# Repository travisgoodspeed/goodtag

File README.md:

# GoodTag

Howdy y'all!

For a long while I've been interested in the RF430FRL152H, which is a
passive RFID tag for 13.56 MHz built around an MSP430 microcontroller.
As few open source examples were available, I found myself first
building a development kit

In this repository, and its
[wiki](https://github.com/travisgoodspeed/goodtag/wiki), you will find
examples and documentation for programming this fine chip, as well as
CAD for hardware boards that use the chip.  This should help you build
your own NFC Type V (ISO 15693) sensor tags, or to emulate existing ones.

This project cannot implement ISO 7816 or ISO 14443 interfaces of
older NFC tags.  For that, you probably need a board designed around
the LPC8N04 or some other microcontroller.

It has partial support for the RF430TAL152H chip found in some medical
devices, written as part of a research project with Axelle Apvrille,
which we presented as [The Inner Guts of a Connected Glucose Sensor
for
Diabetes](https://github.com/cryptax/talks/blob/master/BlackAlps-2019/glucose-blackalps2019.pdf)
at BlackAlps 2019.

73 from Yverdon les Bains,

--Travis Goodspeed

## Getting Started

See the
[GettingStarted](https://github.com/travisgoodspeed/goodtag/wiki/GettingStarted)
page of the wiki for details on how to begin.  You will need an
assembled board, a Linux shell account, and a recent Android phone,
such as the Pixel 3.

## Toolchain

The C examples in this project *must* be compiled with TI's branch of
[GCC for
MSP430](http://software-dl.ti.com/msp430/msp430_public_sw/mcu/msp430/MSPGCC/latest/index_FDS.html).
We sadly cannot be compatible with the GCC4 branch shipped with Debian
because the function calling conventions are incompatible with the
mask ROM.  You will need both the toolchain and its support files.

See my [GoodV](https://github.com/travisgoodspeed/GoodV) project for
an example Android app that communicates with the chip over NfcV.  It
can write firmware to the tags in the TI-TXT format, as well as dump
their existing contents.

For convenient programming from Linux, the [GreatFET
Hydrangea](https://github.com/travisgoodspeed/hydrangea/) board ought
to be handy.  We'll tie it into the `Makefile` once that project is
functional.

## Documentation

An extensive [goodtag
wiki](https://github.com/travisgoodspeed/goodtag/wiki) covers such
nifty topics as the
[RF430FRL152H](https://github.com/travisgoodspeed/goodtag/wiki/RF430FRL152H)
chip, the contents of [its
ROM](https://github.com/travisgoodspeed/goodtag/wiki/ROM), and the use
of its brother, the otherwise undocumented
[RF430TAL152H](https://github.com/travisgoodspeed/goodtag/wiki/RF430TAL152H).

Axelle Apvrille and Travis Goodspeed presented [The Inner Guts of a
Connected Glucose
Sensor](https://github.com/cryptax/talks/blob/master/BlackAlps-2019/glucose-blackalps2019.pdf)
at BlackAlps 2019, describing a medical sensor that uses the
[RF430TAL152H](https://github.com/travisgoodspeed/goodtag/wiki/RF430TAL152H).

## Firmware

In the `firmware/` directory, you will be find a few example projects.
Most of them are designed to compile as patches to the ROM, hooking
NFC commands rather than being called through the `RESET` vector, so
it's important to remember that global and static variables will *not*
be initialized.

You will probably want to start with `hello.c` and then add your own
vendor extension commands.  `gcmemu.c` is an unfinished emulator for
a commercial glucose sensor tag, and `ndef.c` is an NFC business card
in the NDEF format, which can be read by the
[Decode](https://apps.apple.com/us/app/decode-nfc-scanner/id964303354)
app on an iPhone.

Unlike large applications in which multiple modules are linked
together, this project is organized as individually executable modules
that share no code with one another.  This is considered necessary,
given the pitiful amounts of FRAM code memory.

## Shellcode

In the `shellcode/` directory, you will find short examples of code
that can be run ephemerally from SRAM, without permanent changes to
the target.  See the [Shellcode
page](https://github.com/travisgoodspeed/goodtag/wiki/Shellcode) of
the wiki for a more detailed explanation.

## Hardware Designs

For development, I began by using the
[RF430FRL152HEVM](http://www.ti.com/tool/RF430FRL152HEVM) and
[RF430-TMPSNS-EVM](http://www.ti.com/tool/RF430-TMPSNS-EVM) kits from
Texas Instruments.

As these are now in short supply, I've designed the
[GoodTag11](https://github.com/travisgoodspeed/goodtag/wiki/GoodTag11)
in Kicad as my own development kit.  Expect future designs in this
series.

## Related Projects

[GoodV](https://github.com/travisgoodspeed/GoodV) is an Android app
for interacting with RF430FRL152H devices.  You will probably develop
first with JTAG and then use this to flash your code from a handy
phone.

[The GoodTag Wiki](https://github.com/travisgoodspeed/goodtag/wiki)
contains plenty of documentation about the RF430FRL152H and related
chips.

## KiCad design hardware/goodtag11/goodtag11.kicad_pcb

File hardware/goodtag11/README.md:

Howdy y'all,

The GoodTag11 is my attempt at an NFC tag emulator, based around the
RF430FRL152H chip.

The passive values roughly come from the Texas Instruments reference
design in SLOA247C.  I've brought a few pins out unnecessarily, in
case bodge wires are needed, but they will be more firmly grounded in
future designs.

Manufacture in 2layers, 0.024" thickness, FR4-TG130, 1oz, Immersion
Silver, BLACK SOLDER MASK, TWO SIDE MASK, WHITE SILK SCREEN, TOP SILK,
Complex Shape, 8.560cm x 5.398cm.

--Travis

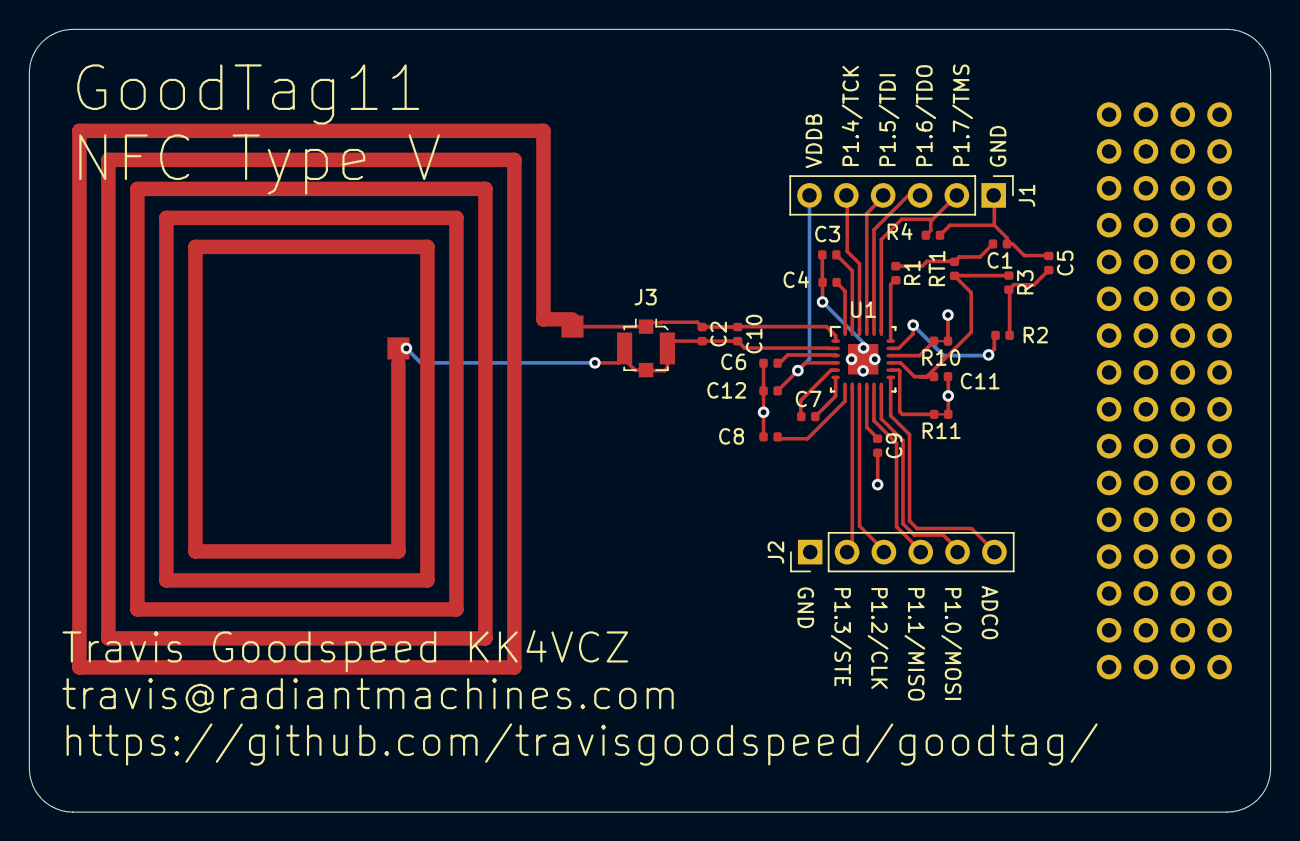
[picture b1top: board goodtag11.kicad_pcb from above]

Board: 2 copper layers, 85.6 x 54.0 mm, 32 parts (0 on the bottom side), 27 nets.

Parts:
 : proto1x8
 #2,  #3,  #4,  #5,  #6,  #7,  #8: proto1x8
C1, C5: 22pF; C_0402_1005Metric
C2: 91pF; C_0402_1005Metric
C3, C4, C8, C12: 100nF; C_0402_1005Metric
C6: 2.2µF; C_0402_1005Metric
C7, C9: 10nF; C_0402_1005Metric
C10: DNP; C_0402_1005Metric
C11: 1µF; C_0402_1005Metric
J1: JTAG; PinHeader_1x06_P2.54mm_Vertical
J2: GPIO; PinHeader_1x06_P2.54mm_Vertical
J3: U.FL; U.FL_Molex_MCRF_73412-0110_Vertical
L1: Antenna; GW10ANT
R1, R2: 1K; R_0402_1005Metric
R3: 100K; R_0402_1005Metric
R4: 10K; R_0402_1005Metric
R10, R11: DNP; R_0402_shorted
RT1: 100K; R_0402_1005Metric
U1: RF430FRL152; RF430FRL152H

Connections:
/ADC0: J2.6, U1.13
/P1.0: J2.5, U1.12
/P1.1: J2.4, U1.11
/P1.2: J2.3, U1.9
/P1.3: J2.2, U1.8
/SVSS: C11.2, R3.1, RT1.1, U1.15
/TCK: J1.5, U1.22
/TDI: J1.4, U1.21
/TDO: J1.3, U1.20
/TMP_REF: R2.2, U1.17
/TMP_THERM: R1.2, U1.18
/TMS: J1.2, R4.1, U1.19
/VDDB: C12.2, J1.6, U1.4
GND: C1.1, C3.2, C4.2, C5.1, C6.2, C8.2, C9.2, C11.1, C12.1, J1.1, J2.1, R4.2, R10.1, R11.1, U1.25
unnamed: C1.2, R1.1, RT1.2
unnamed: C3.1, U1.23
unnamed: C4.1, U1.24
unnamed: C5.2, R2.1, R3.2
unnamed: C6.1, U1.3
unnamed: C7.1, U1.5
unnamed: C7.2, U1.6
unnamed: C8.1, U1.7
unnamed: C9.1, U1.10
unnamed: C2.1, C10.1, J3.1, L1.1, U1.1
unnamed: C2.2, C10.2, J3.2, L1.2, U1.2
unnamed: R10.2, U1.16
unnamed: R11.2, U1.14

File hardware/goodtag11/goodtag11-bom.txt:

Designator	Package			QTY	Designation		Digikey
U1		RF430FRL152H		1	RF430FRL152		296-42545-1-ND
C1,C5		0402 (1005 metric)	2	22pF			311-1018-1-ND
RT1		0402 (1005 metric)	2	100K Thermistor		490-2404-1-ND
R3		0402 (1005 metric)	2	100K			P100KDECT-ND
R1,R2		0402 (1005 metric)	2	1K			YAG1234CT-ND
C2		0402 (1005 metric)	1	91pF			311-3756-1-ND
R4		0402 (1005 metric)	1	10K			RR05P10.0KDCT-ND
C3,C4,C8,C12	0402 (1005 metric)	4	100nF			1276-1004-1-ND
C11		0402 (1005 metric)	1	1µF			1276-1235-1-ND
C7,C9		0402 (1005 metric)	2	10nF			311-1014-1-ND
C6		0402 (1005 metric)	1	2.2µF			587-3153-1-ND


Notes:

1) Do not populate the pin headers or the U.FL antenna connector.

2) The sum of C2 and C10 should be roughly 88pF.  I used four 22pF
   caps to verify this, but one 91pF cap on C2 will probably work just
   fine when C10 is not populated.  Wildly inaccurate tuning will
   produce a tag that works with some readers, but not others.

3) R10 and R11 were 0 Ohm resistors in the prior revision.  Now, they
   are shorted in the copper layer.  If you need to experiment with
   those pins, cut the trace and fly-wire the 0402 pad.

4) This revision of the PCB does not support a battery.  Later
   versions might add an optional one.

5) The RF430FRL152 is the most featureful, but in mass production for
   a specific application, you can probably save some money by
   substituting the FRL153 or 154.

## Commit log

2019-11-08 Initial commit of the public repo.
2019-11-12 Link to slides.
2019-11-22 Link to getting started.
2020-01-02 GoodTag11 photo in the README.
